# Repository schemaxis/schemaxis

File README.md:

# Schemaxis

Managed CLI runs and Studio cases support [packaged application modules](docs/application-modules.md),
including per-app container dispatch, offline archives and reviewed cache cleanup.
Modules require qualified image manifests; no public image catalogue is bundled.

**Declared, repeatable pipelines across engineering and creative desktop
applications, for people and AI agents, with retained evidence used to check
each result.**

<p align="center"><sub>One recorded run: ParaView extracts a surface from a
1.23-million-cell OpenFOAM case, Blender renders an orbit, and FFmpeg encodes the
movie. Every image is retained with its SHA-256 digest.
<a href="docs/release-evidence.md">How it was produced</a>.</sub></p>

You describe the work in JSON or YAML: build this CAD part, mesh it with named
boundary faces, and measure the mesh in ParaView. Schemaxis checks the
description against each application's declared contract and plans it without
starting anything. It then runs each step in the real native application,
in its own process, and keeps the plan, the editable files, the logs and the
verification receipts. If a result fails its checks, nothing downstream is
published as if it had succeeded.

```text
FreeCAD  ──STEP──▶  Gmsh  ──MSH/VTU──▶  ParaView
  editable FCStd      named faces         measured volume and cell sizes
  ✔ reopened          ✔ verified          ✔ checked against the declared solid
```

Schemaxis is a public preview (0.x). Input contracts may still change between
minor versions; migration notes are in the [changelog](CHANGELOG.md).

## Why

- **One language across applications.** A single declared document format,
  with schemas, editor completion and planning, across the registered applications.
- **Native results, not imitations.** Every step runs in the application's own
  runtime: pvbatch, Blender in the background, FreeCAD, Gmsh Python, ngspice and
  so on. You get the files those applications would make.
- **Evidence you can check.** Runs keep their inputs, artifacts, logs and
  digests. `schemaxis verify` rechecks a retained run. Many adaptors add
  independent checks, such as beam theory, closed-form circuit responses,
  analytic volumes and frame-by-frame decoding.
- **Resume without redoing, and without mixing.** Rerunning an unchanged workflow
  with `--resume` reuses each completed job whose inputs can be proven unchanged,
  and records which were reused; jobs whose external inputs cannot be fingerprinted,
  such as ParaView case readers, run again. A changed workflow is refused for
  resume, not quietly mixed with old results.
- **Built for AI agents as well as people.** Agents get the same discovery,
  description, planning and verification as humans, through the CLI or a local
  JSON-lines agent service. In our ParaView pilot, smaller models that failed
  the task on their own passed every check when they used Schemaxis. Frontier
  models did not need it, and were slower with it. See the
  [measured results](https://schemaxis.io/measured-results.html) and their limits.

## Install

Schemaxis needs Python 3.10 or newer and has no runtime dependencies.

```bash
git clone https://github.com/schemaxis/schemaxis.git
cd schemaxis
python3 -m pip install .         # or: python3 -m pip install '.[yaml]' for YAML
schemaxis discover              # list every adaptor and its contract
```

Install from the source repository for this preview. A PyPI package release is
separate from publication of the repository.

From a source checkout, without installing:

```bash
git clone https://github.com/schemaxis/schemaxis.git
cd schemaxis
export PYTHONPATH=src
python3 -m schemaxis discover
```

The applications themselves are installed separately. Record where they are
once with `schemaxis configure`. See [installation](docs/installation.md).

## Five minutes, no applications needed

```bash
schemaxis describe --provider freecad               # operations and options
schemaxis plan examples/schemaxis/freecad-bracket.json
```

`plan` validates the document and resolves every option without starting
FreeCAD. Change a value in the example to something invalid and plan again:
the fault names the field and explains how to fix it. When FreeCAD is
configured, `schemaxis run` performs the work and `schemaxis verify` rechecks it.
The [ten-minute walkthrough](docs/getting-started.md) continues from here.

For interactive work, Schemaxis Studio runs locally in your browser:

```bash
schemaxis console --workspace .schemaxis/studio --web
```

## MCP for agents

Launch a local stdio MCP server with an owned session workspace:

```bash
schemaxis mcp --workspace .schemaxis/agent-session
```

Agents can discover tools, capture plans, poll jobs and read verification
evidence through the same execution service. The default profile admits the
reviewed file-free SymPy exact-root route and bounded compositions of that route;
native execution requires its separately configured runtime. Other authored
routes are refused until reviewed. Input admission is not an OS sandbox.

Modern and legacy MCP Python clients and the OpenAI Agents SDK passed local
list/call/host-plan checks; Claude Agent SDK passed connection and tool discovery.
No model requests were made. A separate follow-up through both MCP modes and the
OpenAI wrapper executed and freshly verified real local SymPy jobs. See the
[agent quickstart](docs/agent-quickstart.md), [MCP guide](docs/mcp.md) and
[exact SDK versions and limits](verification/2026-10-29-mcp-clients.md).

## Applications

| Area | Applications |
| --- | --- |
| CFD and data post-processing | ParaView (serial and MPI pvbatch, OpenFOAM-format cases) |
| CAD, meshing and structures | FreeCAD (editable through-all and finite-depth machining), Gmsh, CalculiX, OpenSees (planar elastic trusses), meshio (bounded triangle/tetra/hexahedral VTU/VTK interchange), OpenSCAD (dimensioned plates and spacers) |
| Solid heat and scalar conduction | Elmer (layered steady solid heat), GetDP (layered steady heat/current) |
| Numerical analysis | GNU Octave, R, Cantera (thermodynamics, equilibrium and closed reactors with optional fixed-bath thermal exchange), ngspice |
| PCB inspection | KiCad |
| Fabrication | PrusaSlicer |
| Scientific imaging | ImageJ, ImageMagick (bounded PNG preparation and comparison sheets), WebP (exact RGBA lossless assets, opaque lossy assets with checked error and byte budgets, and static WebP-to-PNG decoding) |
| Spreadsheets | LibreOffice Calc (ODS and XLSX) |
| Reports | Pandoc (structured reports, verified PNG artifact handoffs and timed transcripts to HTML/DOCX, with optional checked EPUB 3 publication), EPUBCheck (fresh standards checks of captured EPUBs) |
| Data and plots | SQLite (typed relational summaries), Apache Arrow (typed nullable CSV to verified Parquet), Gnuplot (CSV plots with checked geometry) |
| PDF assembly and review | QPDF (selected pages, order, repeats and quarter turns), MuPDF (ordered page images, text and geometry) |
| 3D, games and pixel art | Blender, Godot, Aseprite |
| Diagrams, video and media | Inkscape, FFmpeg (verified video, captioned review movies, AAC-to-WAV extraction and bounded WAV-to-AAC publication), Shotcut, Adobe Premiere Pro (experimental, read-only) |
| Directed graph layout | Graphviz (checked DOT/SVG layout) |
| Audio | SoX (PCM16 edits, measured peak headroom and speech-ready mono 16 kHz preparation), FLAC (lossless recording archives with optional declared title, artist and description labels, and PCM16 handoffs), whisper.cpp (draft transcripts and captions with optional declared text corrections, cue deletion, cue timing edits and bounded word-preserving line layout), eSpeak NG (offline synthetic draft narration with US English, British English, French and Spanish voice choices) |
| Publication bundles | Info-ZIP (selected publication files in a stored ZIP with an independently checked byte inventory) |
| Geospatial | QGIS, GDAL (checked raster windows and nearest grid resizing) |
| Photo metadata | ExifTool (typed read, audit and comparison of JPEG, TIFF, DNG, PNG, WebP, HEIF and XMP sidecar metadata; new copies with edited or removed metadata (JPEG, TIFF, DNG, PNG, WebP and the existing items of HEIF files) or minimised JPEG, PNG and WebP metadata, corrected capture times, declared positions or positions interpolated on GPX tracks and typed metadata copied from a photo or an XMP sidecar onto new copies, in every one of those containers, portable XMP sidecars exported, and photo names planned and exact foldered copies organised, each proved by independent readback or recomputation; originals are never modified) |

Each adaptor declares its bounded scope, so it is explicit about what it does
*not* do. Run `schemaxis discover` for the details, or see the
[coverage report](docs/coverage.md). Adaptors can also be installed as separate
packages: see "External adaptor packages" in the
[adaptor development guide](docs/adaptor-development.md).

## Documentation

- [Getting started](docs/getting-started.md) and the [user guide](docs/user-guide.md)
- [JSON input reference](docs/json-input.md), [YAML authoring](docs/yaml.md) and the [schema guide](docs/schema-guide.md)
- [Studio](docs/visual-console.md) and [console commands](docs/console.md)
- [CLI and topic help](docs/cli-discovery.md), [headless operation](docs/headless.md),
  [shared schemas](docs/schema-storage.md) and [storage inspection/backups](docs/storage-management.md)
- [Guide for AI agents](docs/ai-guide.md) and the [agent service](docs/agent-service.md)
- [CFD post-processing with ParaView](docs/cfd-guide.md)
- [Workflow benchmarks and reproducibility](docs/benchmarks.md), and [release evidence](docs/release-evidence.md)
- [Capabilities in detail](docs/capabilities.md) and the [quick reference](docs/quick-reference.md)
- [Checked FreeCAD imports and exports](docs/freecad.md), [parametric parts](docs/freecad-part-design.md)
  and [fixed assemblies](docs/freecad-assemblies.md)
- [Developer guide](docs/developer-guide.md) and [adaptor development](docs/adaptor-development.md)

## Platform support

Schemaxis is developed and natively qualified on Linux x86-64. macOS and Windows
are not yet supported: the host framework is pure Python, but parts of it still
assume a POSIX system, and no native adaptor has been qualified there.

## Contributing

Issues and pull requests are welcome. See [CONTRIBUTING.md](CONTRIBUTING.md)
and [AGENTS.md](AGENTS.md). Please report security issues privately, as
described in [SECURITY.md](SECURITY.md).

Schemaxis was conceived, designed and developed by David L. F. Gaden, with the
help of AI coding assistants working under his direction and review.

## Licence

Copyright © 2026 David L. F. Gaden. Licensed under the
[Apache License 2.0](LICENSE). Third-party material keeps its own licence: see
[NOTICE](NOTICE) and [LICENSES/](LICENSES).

Core and Studio include general-purpose database adaptors, geometry, meshing,
local case files and workflow execution. Integrated database-backed case/history
services and CFD solver/case-preparation integrations are separate components.
See [Distribution boundary](docs/distribution.md).

"Schemaxis" is a trademark of David L. F. Gaden (application pending). See
[TRADEMARKS.md](TRADEMARKS.md). ParaView, Blender, FreeCAD and the other
application names are trademarks of their respective owners. Their use here
does not imply endorsement.

## Independent artifact viewer

Run `schemaxis-viewer /path/to/results` (or
`PYTHONPATH=src python3 -m schemaxis_viewer` from this checkout) to browse local
files and folders as galleries, animated sequences, XYZ stacks and registered
3D image planes. It also previews STL/OBJ meshes, browser-supported media,
CSV/TSV tables and searchable text. The viewer has no Schemaxis runtime imports
or third-party dependencies. Studio embeds the same viewer in Results and
automatically loads completed Case Runner output. Open/Add folder actions,
subfolder controls, type filters, relative-path navigation, recent collections,
bulk preview selection and light/dark/system themes work in both entry points.
See the [viewer guide](docs/artifact-viewer.md)
for supported formats, metadata and preview limits.

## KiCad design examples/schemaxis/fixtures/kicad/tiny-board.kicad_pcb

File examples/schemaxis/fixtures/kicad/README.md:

# KiCad board fixtures

Four original two-layer boards written by hand for the `schemaxis.kicad/1` adaptor and
saved in the KiCad 10.0 board format with `kicad-cli pcb upgrade --force` (KiCad
10.0.7). They contain no third-party library footprints: every footprint is inline.
Each `.kicad_pro` declares a 0.2 mm Default netclass clearance and sets
`lib_footprint_issues`/`lib_footprint_mismatch` to `ignore`, because the inline
footprints are not in any library.

- `tiny-board`: baseline, clean DRC.
- `tiny-variant`: different outline, rotation, nets, vias and holes; clean DRC.
- `tiny-clearance`: baseline plus an AUX net 0.1 mm from GND; two clearance errors.
- `tiny-open`: baseline without one GND track; one unconnected item.

Expected counts and geometry are derived from the declared coordinates in
[`docs/kicad.md`](../../../../docs/kicad.md#fixtures), not from KiCad output. These
are input data. Source-bound qualification includes their bytes, so editing them
invalidates the KiCad receipt; review geometry and expectations together.

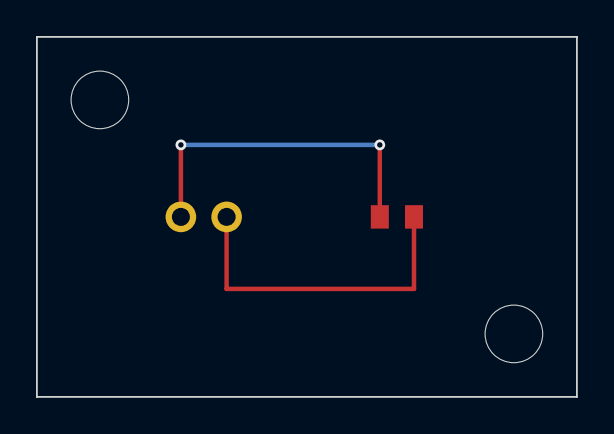
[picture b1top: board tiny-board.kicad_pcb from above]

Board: 2 copper layers, 30.0 x 20.0 mm, 4 parts (0 on the bottom side), 2 nets.

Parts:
H1, H2: M3; MountingHole_3.2mm
J1: Conn_01x02; Header_1x02_P2.54mm
R1: 1k; R_0805

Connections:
GND: J1.2, R1.2
SIG: J1.1, R1.1
